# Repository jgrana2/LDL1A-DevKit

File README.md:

Life Data Link vital signs development kit project files.

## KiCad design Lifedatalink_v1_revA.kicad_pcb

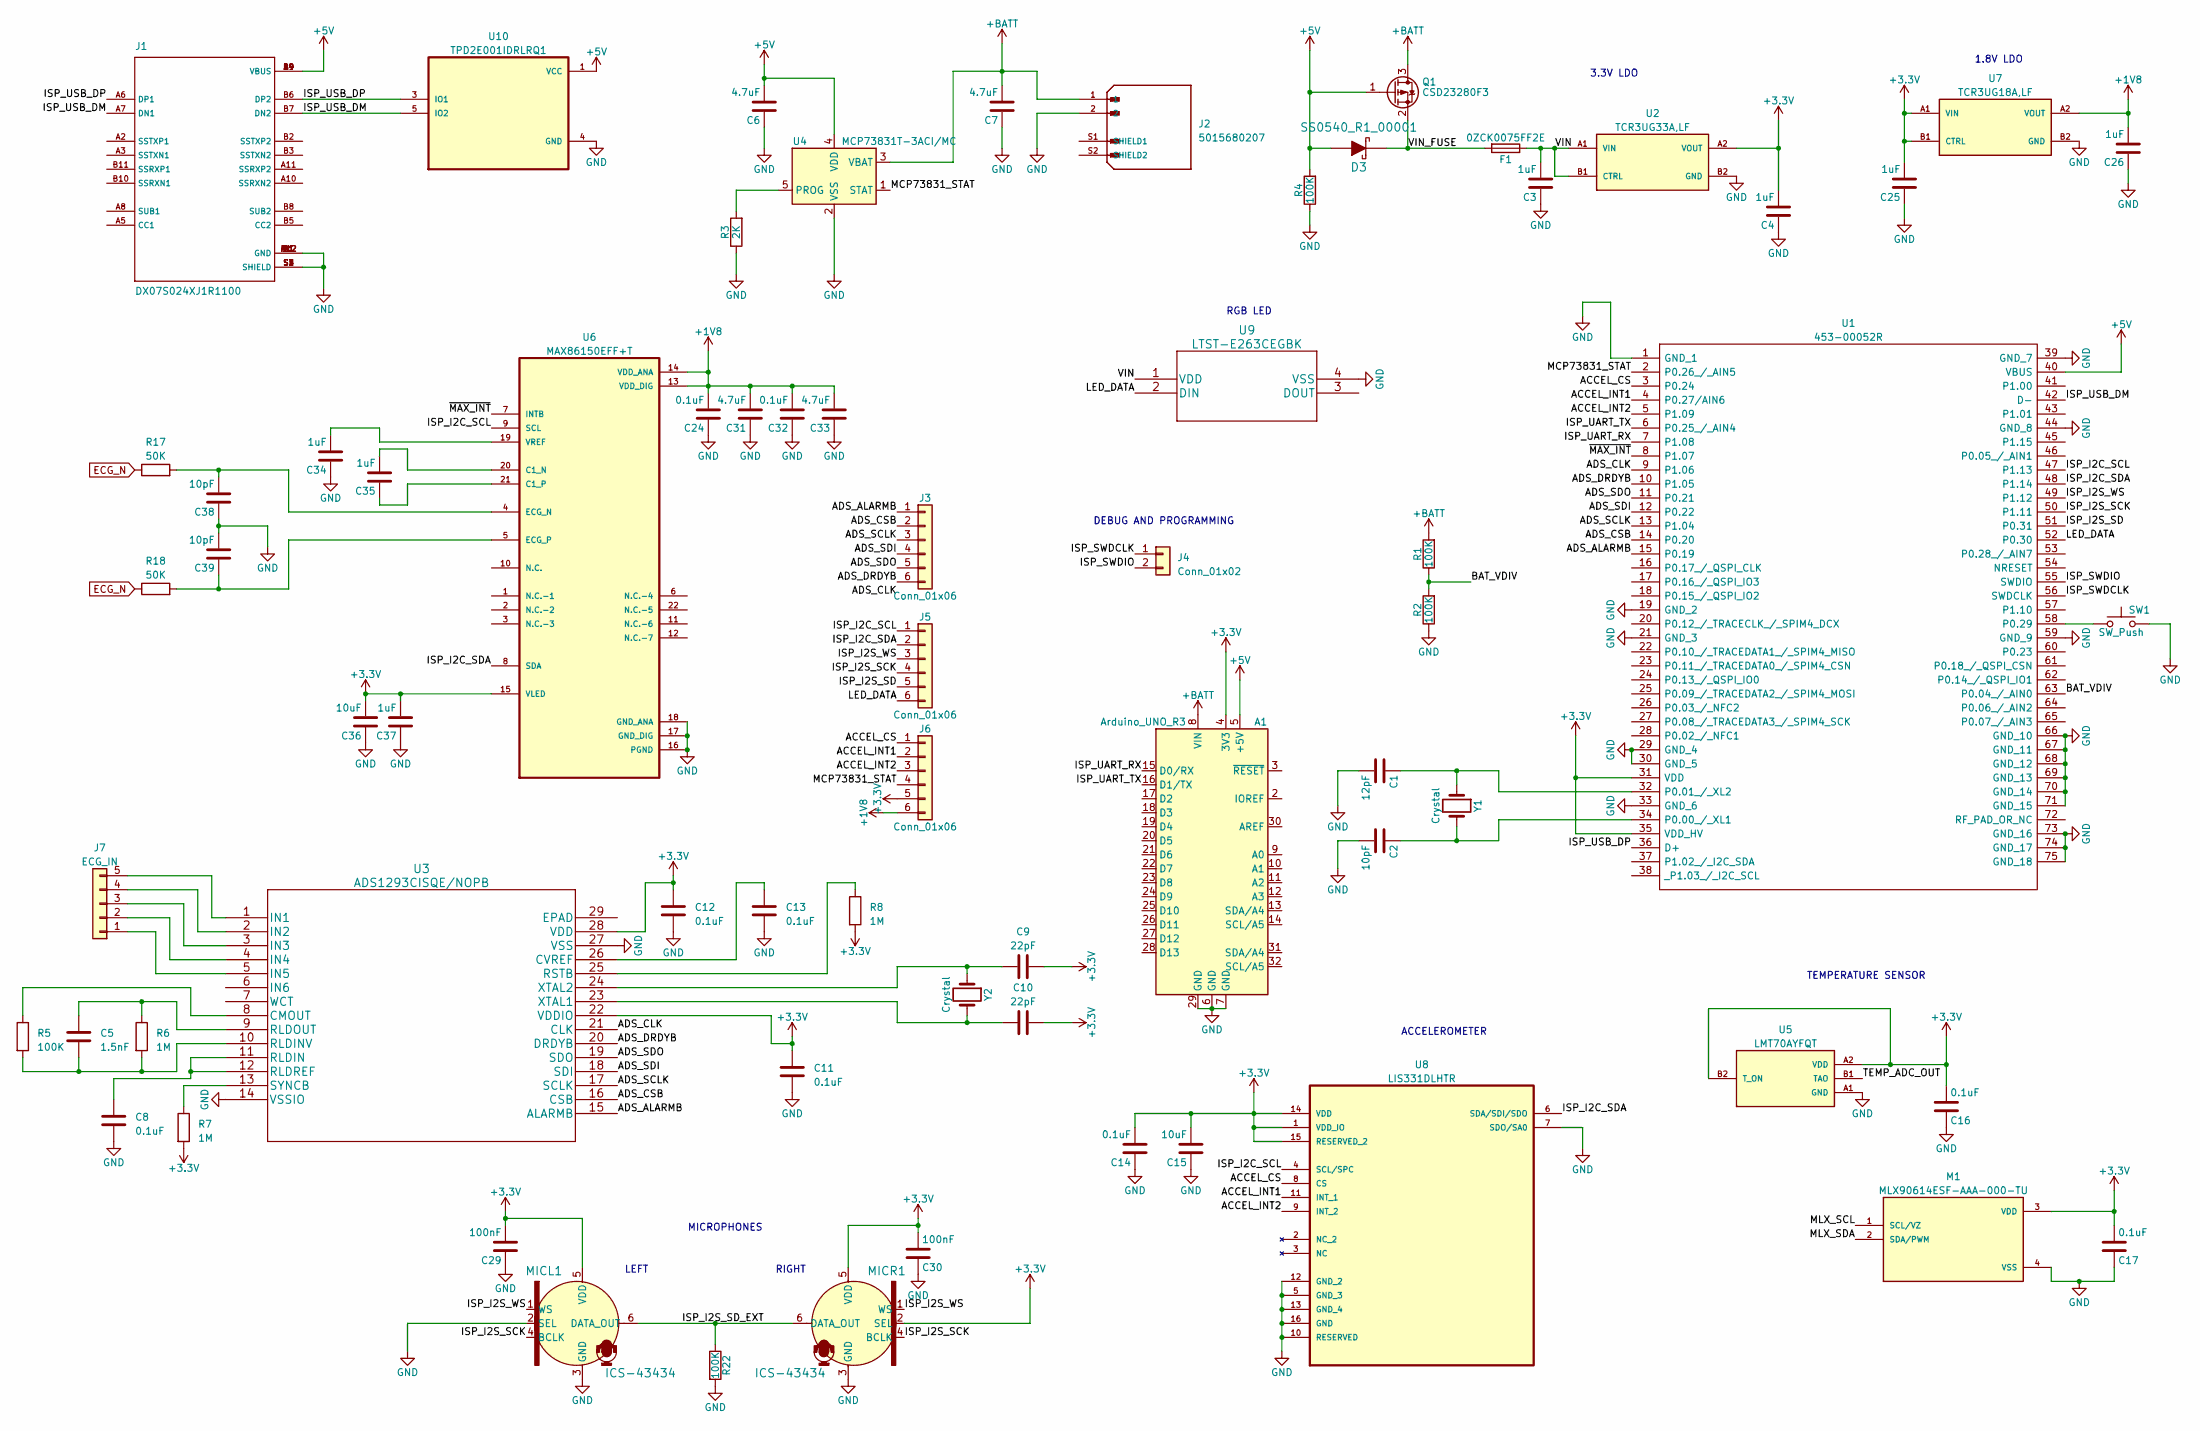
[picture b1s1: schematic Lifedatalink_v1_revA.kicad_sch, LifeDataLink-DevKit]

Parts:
A1: Arduino_UNO_R3
C1: 12pF; C_0402_1005Metric; MPN C0402C120J5GACTU
C2: 10pF; C_0402_1005Metric; MPN C0402C100J5GACTU
C3, C4, C25, C26, C34, C35, C37: 1uF; C_0402_1005Metric; MPN C0402C105K9PACTU
C5: 1.5nF; C_0402_1005Metric
C6, C7: 4.7uF; C_0402_1005Metric; MPN C0402C475M7PACTU
C8, C11, C12, C13: 0.1uF; C_0402_1005Metric
C9, C10: 22pF; C_0402_1005Metric
C14: 0.1uF; C_0402_1005Metric; MPN C0402C106M9PAC7867
C15: 10uF; C_0402_1005Metric; MPN C0402C106M9PAC7867
C16, C17: 0.1uF; C_0402_1005Metric; MPN C0402C104K4PACTU
C24, C32: 0.1uF; C_0402_1005Metric; MPN C0402C105K9PACTU
C29, C30: 100nF; C_0402_1005Metric; MPN C0402C104K4PACTU
C31, C33: 4.7uF; C_0402_1005Metric; MPN C0402C105K9PACTU
C36: 10uF; C_0402_1005Metric; MPN C0402C105K9PACTU
C38, C39: 10pF; C_0402_1005Metric; MPN C0402C105K9PACTU
D3: SS0540_R1_00001; D_SOD-123; MPN SS0540_R1_00001; Digi-Key_PN 3757-SS0540_R1_00001CT-ND
F1: 0ZCK0075FF2E; Fuse_0805_2012Metric; MPN 0603L075SLYR
J1: DX07S024XJ1R1100; JAE_DX07S024XJ1R1100; MPN DX07S024XJ1R1100
J2: 5015680207; MOLEX_5015680207; PARTREV A
J3, J5, J6: Conn_01x06; 1.27mm_pads_01x06
J4: Conn_01x02; PinHeader_1x02_P2.54mm_Vertical
J7: ECG_IN; PinHeader_1x05_P2.54mm_Horizontal
M1: MLX90614ESF-AAA-000-TU; TO254P940H1340-4; PARTREV 13
MICL1: ICS-43434; MIC_ICS-43434; MPN ICS-43434
MICR1: ICS-43434; MIC_ICS-43434; MPN ICS-43434
Q1: CSD23280F3; TRANS_CSD23280F3; MPN CSD23280F3
R1, R2, R4, R22: 100K; R_0402_1005Metric; MPN CRCW0402100KFKEDC
R3: 2K; R_0402_1005Metric; MPN CRCW040210K0FKEDC
R5: 100K; R_0402_1005Metric
R6, R7, R8: 1M; R_0402_1005Metric
R17, R18: 50K; R_0402_1005Metric
SW1: SW_Push; SW_B3U-3000P; MPN B3U-3000P
U1: 453-00052R; 45300052R; Mouser Part Number 239-453-00052R
U2: TCR3UG33A,LF; BGA4N35P2X2_64X64X33; PARTREV 2021-10-28
U3: ADS1293CISQE/NOPB; ADS1293CISQE
U4: MCP73831T-3ACI/MC; DFN-8-1EP_3x2mm_P0.5mm_EP1.3x1.5mm; MPN MCP73831T-3ACI/MC
U5: LMT70AYFQT; BGA4C40P2X2_88X88X68
U6: MAX86150EFF+T; XDCR_MAX86150EFF+
U7: TCR3UG18A,LF; BGA4N35P2X2_64X64X33; PARTREV 2021-10-28
U8: LIS331DLHTR; LGA16R50P3X5_300X300X100; MPN LIS331DLHTR
U9: LTST-E263CEGBK
U10: TPD2E001IDRLRQ1; SOT50P160X60-5N
Y1, Y2: Crystal; ABS05-32.768KHZ-T; MPN ABS05-32.768KHZ-9-T

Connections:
+1V8: C24.2, C26.2, C31.2, C32.2, C33.2, J6.6, U6.13 (VDD_DIG), U6.14 (VDD_ANA), U7.A2 (VOUT)
+3V3: A1.4 (3V3), C4.2, C9.2, C10.2, C11.2, C12.2, C14.2, C15.2, C16.2, C17.2, C25.2, C29.2, C30.2, C36.2, C37.2, J6.5, M1.3 (VDD), MICL1.5 (VDD), MICR1.2 (SEL), MICR1.5 (VDD), R7.2, R8.2, U1.31 (VDD), U1.35 (VDD_HV), U2.A2 (VOUT), U3.22 (VDDIO), U3.28 (VDD), U5.A2 (VDD), U5.B2 (T_ON), U6.15 (VLED), U7.A1 (VIN), U7.B1 (CTRL), U8.1 (VDD_IO), U8.14 (VDD), U8.15 (RESERVED_2)
+5V: A1.5 (+5V), C6.2, D3.2, J1.A4 (VBUS), J1.A9 (VBUS), J1.B4 (VBUS), J1.B9 (VBUS), Q1.1 (G), R4.2, U1.40 (VBUS), U4.4 (VDD), U10.1 (VCC)
+BATT: A1.8 (VIN), C7.2, J2.1, Q1.3 (D), R1.2, U4.3 (VBAT)
/ACCEL_CS: J6.1, U1.3 (P0.24), U8.8 (CS)
/ACCEL_INT1: J6.2, U1.4 (P0.27/AIN6), U8.11 (INT_1)
/ACCEL_INT2: J6.3, U1.5 (P1.09), U8.9 (INT_2)
/ADS_ALARMB: J3.1, U1.15 (P0.19), U3.15 (ALARMB)
/ADS_CLK: U1.9 (P1.06), U3.21 (CLK)
/ADS_CSB: J3.2, U1.14 (P0.20), U3.16 (CSB)
/ADS_DRDYB: J3.6, U1.10 (P1.05), U3.20 (DRDYB)
/ADS_SCLK: J3.3, U1.13 (P1.04), U3.17 (SCLK)
/ADS_SDI: J3.4, U1.12 (P0.22), U3.18 (SDI)
/ADS_SDO: J3.5, U1.11 (P0.21), U3.19 (SDO)
/BAT_VDIV: R1.1, R2.2, U1.63 (P0.04_/_AIN0)
/ISP_I2C_SCL: J5.1, U1.47 (P1.13), U6.9 (SCL), U8.4 (SCL/SPC)
/ISP_I2C_SDA: J5.2, U1.48 (P1.14), U6.8 (SDA), U8.6 (SDA/SDI/SDO)
/ISP_I2S_SCK: J5.4, MICL1.4 (BCLK), MICR1.4 (BCLK), U1.50 (P1.11)
/ISP_I2S_SD: J5.5, U1.51 (P0.31)
/ISP_I2S_SD_EXT: MICL1.6 (DATA_OUT), MICR1.6 (DATA_OUT), R22.1
/ISP_I2S_WS: J5.3, MICL1.1 (WS), MICR1.1 (WS), U1.49 (P1.12)
/ISP_SWDCLK: J4.1, U1.56 (SWDCLK)
/ISP_SWDIO: J4.2, U1.55 (SWDIO)
/ISP_UART_RX: A1.15 (D0/RX), U1.7 (P1.08)
/ISP_UART_TX: A1.16 (D1/TX), U1.6 (P0.25_/_AIN4)
/ISP_USB_DM: J1.A7 (DN1), J1.B7 (DN2), U1.42 (D-), U10.5 (IO2)
/ISP_USB_DP: J1.A6 (DP1), J1.B6 (DP2), U1.36 (D+), U10.3 (IO1)
/LED_DATA: J5.6, U1.52 (P0.30), U9.2 (DIN)
/MCP73831_STAT: J6.4, U1.2 (P0.26_/_AIN5), U4.1 (STAT)
/MLX_SCL: M1.1 (SCL/VZ)
/MLX_SDA: M1.2 (SDA/PWM)
/TEMP_ADC_OUT: U5.B1 (TAO)
/VIN: C3.2, F1.1, U2.A1 (VIN), U2.B1 (CTRL), U9.1 (VDD)
/VIN_FUSE: D3.1, F1.2, Q1.2 (S)
/~MAX_INT: U1.8 (P1.07), U6.7 (INTB)
ECG_N: R17.1, R18.1
GND: A1.6 (GND), A1.7 (GND), A1.29 (GND), C1.2, C2.2, C3.1, C4.1, C6.1, C7.1, C8.2, C11.1, C12.1, C13.1, C14.1, C15.1, C16.1, C17.1, C24.1, C25.1, C26.1, C29.1, C30.1, C31.1, C32.1, C33.1, C34.1, C36.1, C37.1, C38.1, C39.2, J1.A1 (GND), J1.A12 (GND), J1.B1 (GND), J1.B12 (GND), J1.S1 (SHIELD), J1.S2 (SHIELD), J1.S3 (SHIELD), J1.S4 (SHIELD), J2.2, M1.4 (VSS), MICL1.2 (SEL), MICL1.3 (GND), MICR1.3 (GND), R2.1, R3.1, R4.1, R22.2, SW1.2, U1.1 (GND_1), U1.19 (GND_2), U1.21 (GND_3), U1.29 (GND_4), U1.30 (GND_5), U1.33 (GND_6), U1.39 (GND_7), U1.44 (GND_8), U1.59 (GND_9), U1.66 (GND_10), U1.67 (GND_11), U1.68 (GND_12), U1.69 (GND_13), U1.70 (GND_14), U1.71 (GND_15), U1.73 (GND_16), U1.74 (GND_17), U1.75 (GND_18), U2.B2 (GND), U3.14 (VSSIO), U3.27 (VSS), U4.2 (VSS), U5.A1 (GND), U6.16 (PGND), U6.17 (GND_DIG), U6.18 (GND_ANA), U7.B2 (GND), U8.5 (GND_3), U8.7 (SDO/SA0), U8.10 (RESERVED), U8.12 (GND_2), U8.13 (GND_4), U8.16 (GND), U9.4 (VSS), U10.4 (GND)
unnamed: J7.1, U3.5 (IN5)
unnamed: J7.2, U3.4 (IN4)
unnamed: J7.3, U3.3 (IN3)
unnamed: J7.4, U3.2 (IN2)
unnamed: J7.5, U3.1 (IN1)
unnamed: C2.1, U1.34 (P0.00_/_XL1), Y1.2
unnamed: C1.1, U1.32 (P0.01_/_XL2), Y1.1
unnamed: SW1.1, U1.58 (P0.29)
unnamed: R5.1, U3.8 (CMOUT)
unnamed: C13.2, U3.26 (CVREF)
unnamed: C8.1, U3.11 (RLDIN), U3.12 (RLDREF)
unnamed: C5.2, R5.2, R6.2, U3.10 (RLDINV)
unnamed: C5.1, R6.1, U3.9 (RLDOUT)
unnamed: R8.1, U3.25 (RSTB)
unnamed: R7.1, U3.13 (SYNCB)
unnamed: C10.1, U3.23 (XTAL1), Y2.2
unnamed: C9.1, U3.24 (XTAL2), Y2.1
unnamed: R3.2, U4.5 (PROG)
unnamed: C35.2, U6.20 (C1_N)
unnamed: C35.1, U6.21 (C1_P)
unnamed: C38.2, R17.2, U6.4 (ECG_N)
unnamed: C39.1, R18.2, U6.5 (ECG_P)
unnamed: C34.2, U6.19 (VREF)

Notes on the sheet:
DEBUG AND PROGRAMMING
RIGHT
3.3V LDO
RGB LED
LEFT
ACCELEROMETER
TEMPERATURE SENSOR
MICROPHONES
1.8V LDO

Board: 4 copper layers, 69 parts (1 on the bottom side), 57 nets, no tracks yet.

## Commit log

2022-04-22 Update schematic components
2022-10-25 Update PCB form factor and place components
2022-10-25 Replace the BLE module with an ISP1807-LR-RS
2022-10-25 Replace the BLE module with a BL5340 (453-00053R)

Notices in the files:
parts and their libraries:
Copyright 2021 Accelerated Designs. All rights reserved.
